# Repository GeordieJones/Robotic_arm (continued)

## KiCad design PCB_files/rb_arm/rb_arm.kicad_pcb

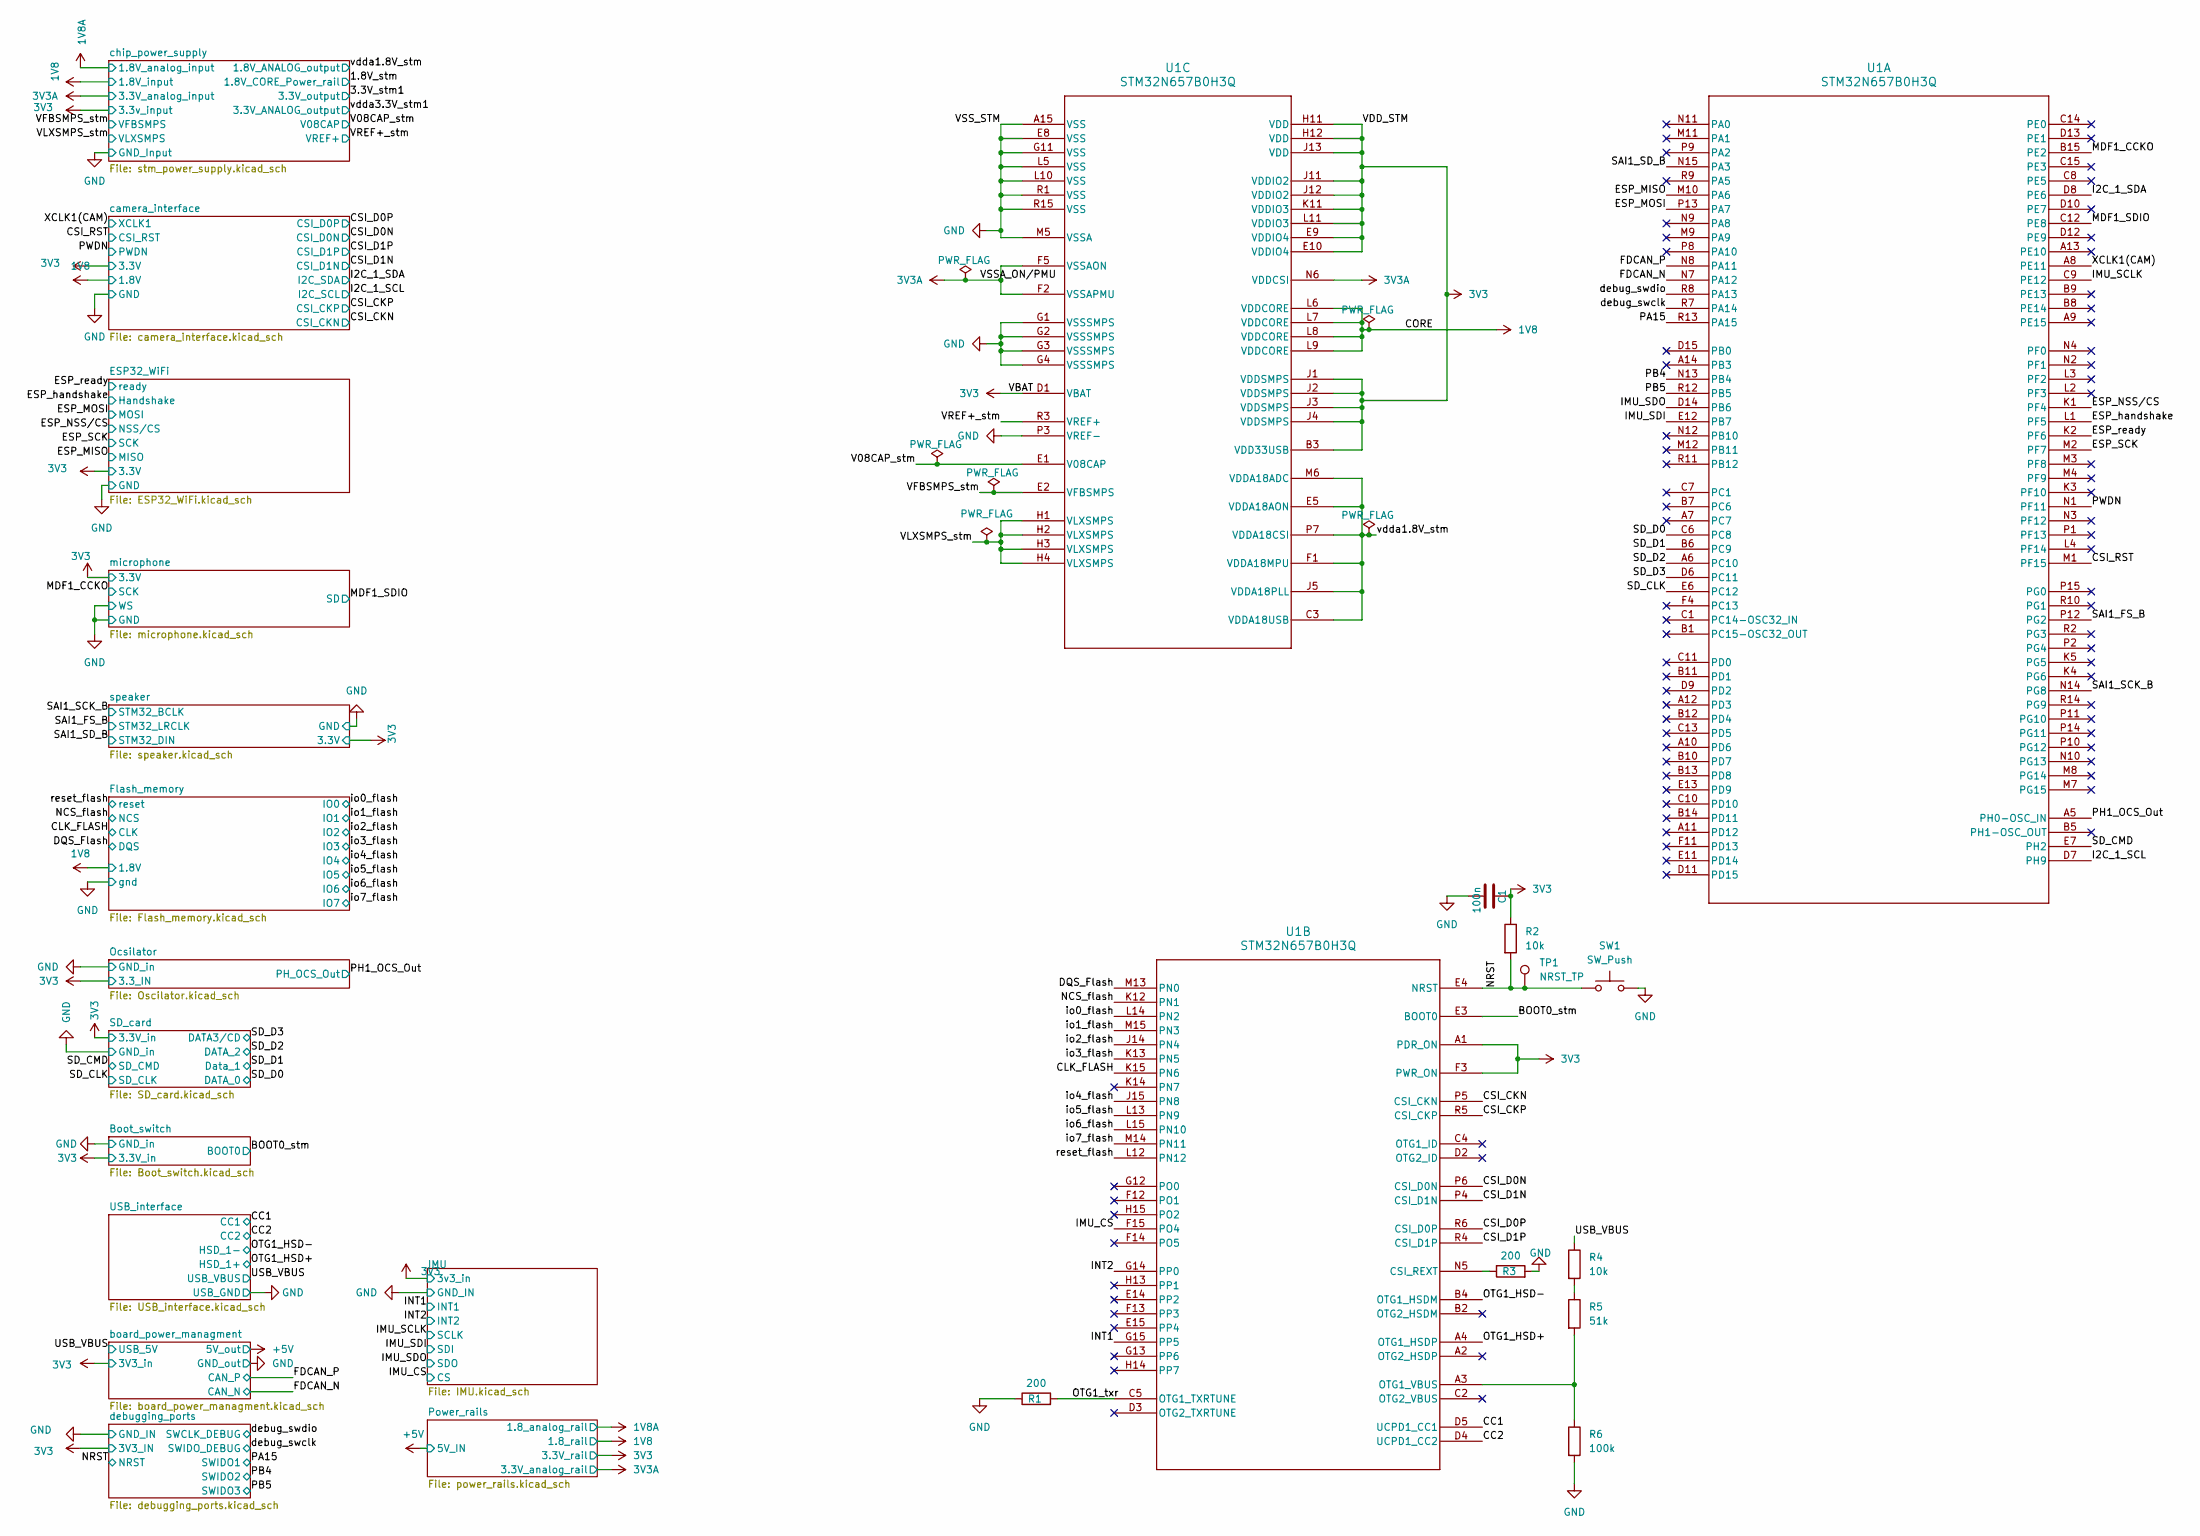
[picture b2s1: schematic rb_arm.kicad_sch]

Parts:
C1: 100n; C_0402_1005Metric; part samsung CL05B104KP5NNNC
R1, R3: 200; R_0402_1005Metric; part number RT0402BRD07200RL
R2, R4: 10k; R_0402_1005Metric; part number Samsung Electro-Mechanics RC1005F103CS
R5: 51k; R_0402_1005Metric; part number YAGEO RC0402FR-0751KL
R6: 100k; R_0402_1005Metric; part number YAGEO RC0402FR-07100KL
SW1: SW_Push; SW_PUSH_6mm_H4.3mm; part number C&K PTS645SM43SMTR92 LFS
TP1: NRST_TP; Pin_D1.0mm_L10.0mm
U1: STM32N657B0H3Q; VFBGA198_10X10_STM

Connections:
1V8: U1.L6 (VDDCORE), U1.L7 (VDDCORE), U1.L8 (VDDCORE), U1.L9 (VDDCORE); also elsewhere on the board
3V3: C1.1, R2.1, U1.A1 (PDR_ON), U1.B3 (VDD33USB), U1.D1 (VBAT), U1.E9 (VDDIO4), U1.E10 (VDDIO4), U1.F3 (PWR_ON), U1.H11 (VDD), U1.H12 (VDD), U1.J1 (VDDSMPS), U1.J2 (VDDSMPS), U1.J3 (VDDSMPS), U1.J4 (VDDSMPS), U1.J11 (VDDIO2), U1.J12 (VDDIO2), U1.J13 (VDD), U1.K11 (VDDIO3), U1.L11 (VDDIO3); also elsewhere on the board
3V3A: U1.F2 (VSSAPMU), U1.F5 (VSSAON), U1.N6 (VDDCSI); also elsewhere on the board
/BOOT0_stm: U1.E3 (BOOT0); also elsewhere on the board
/CC1: U1.D5 (UCPD1_CC1); also elsewhere on the board
/CC2: U1.D4 (UCPD1_CC2); also elsewhere on the board
/CLK_FLASH: U1.K15 (PN6); also elsewhere on the board
/CSI_CKN: U1.P5 (CSI_CKN); also elsewhere on the board
/CSI_CKP: U1.R5 (CSI_CKP); also elsewhere on the board
/CSI_D0N: U1.P6 (CSI_D0N); also elsewhere on the board
/CSI_D0P: U1.R6 (CSI_D0P); also elsewhere on the board
/CSI_D1N: U1.P4 (CSI_D1N); also elsewhere on the board
/CSI_D1P: U1.R4 (CSI_D1P); also elsewhere on the board
/CSI_RST: U1.M1 (PF15); also elsewhere on the board
/DQS_Flash: U1.M13 (PN0); also elsewhere on the board
/ESP_MISO: U1.M10 (PA6); also elsewhere on the board
/ESP_MOSI: U1.P13 (PA7); also elsewhere on the board
/ESP_NSS/CS: U1.K1 (PF4); also elsewhere on the board
/ESP_SCK: U1.M2 (PF7); also elsewhere on the board
/ESP_handshake: U1.L1 (PF5); also elsewhere on the board
/ESP_ready: U1.K2 (PF6); also elsewhere on the board
/FDCAN_N: U1.N7 (PA12); also elsewhere on the board
/FDCAN_P: U1.N8 (PA11); also elsewhere on the board
/I2C_1_SCL: U1.D7 (PH9); also elsewhere on the board
/I2C_1_SDA: U1.D8 (PE6); also elsewhere on the board
/IMU_CS: U1.F15 (PO4); also elsewhere on the board
/IMU_SCLK: U1.C9 (PE12); also elsewhere on the board
/IMU_SDI: U1.E12 (PB7); also elsewhere on the board
/IMU_SDO: U1.D14 (PB6); also elsewhere on the board
/INT1: U1.G15 (PP5); also elsewhere on the board
/INT2: U1.G14 (PP0); also elsewhere on the board
/MDF1_CCKO: U1.B15 (PE2); also elsewhere on the board
/MDF1_SDIO: U1.C12 (PE8); also elsewhere on the board
/NCS_flash: U1.K12 (PN1); also elsewhere on the board
/NRST: R2.2, SW1.1, TP1.1 (1_1), U1.E4 (NRST); also elsewhere on the board
/OTG1_HSD+: U1.A4 (OTG1_HSDP); also elsewhere on the board
/OTG1_HSD-: U1.B4 (OTG1_HSDM); also elsewhere on the board
/OTG1_txr: R1.2, U1.C5 (OTG1_TXRTUNE)
/PA15: U1.R13 (PA15); also elsewhere on the board
/PB4: U1.N13 (PB4); also elsewhere on the board
/PB5: U1.R12 (PB5); also elsewhere on the board
/PH1_OCS_Out: U1.A5 (PH0-OSC_IN); also elsewhere on the board
/PWDN: U1.N1 (PF11); also elsewhere on the board
/SAI1_FS_B: U1.P12 (PG2); also elsewhere on the board
/SAI1_SCK_B: U1.N14 (PG8); also elsewhere on the board
/SAI1_SD_B: U1.N15 (PA3); also elsewhere on the board
/SD_CLK: U1.E6 (PC12); also elsewhere on the board
/SD_CMD: U1.E7 (PH2); also elsewhere on the board
/SD_D0: U1.C6 (PC8); also elsewhere on the board
/SD_D1: U1.B6 (PC9); also elsewhere on the board
/SD_D2: U1.A6 (PC10); also elsewhere on the board
/SD_D3: U1.D6 (PC11); also elsewhere on the board
/USB_VBUS: R4.1; also elsewhere on the board
/V08CAP_stm: U1.E1 (V08CAP); also elsewhere on the board
/VFBSMPS_stm: U1.E2 (VFBSMPS); also elsewhere on the board
/VLXSMPS_stm: U1.H1 (VLXSMPS), U1.H2 (VLXSMPS), U1.H3 (VLXSMPS), U1.H4 (VLXSMPS); also elsewhere on the board
/VREF+_stm: U1.R3 (VREF+); also elsewhere on the board
/XCLK1(CAM): U1.A8 (PE11); also elsewhere on the board
/debug_swclk: U1.R7 (PA14); also elsewhere on the board
/debug_swdio: U1.R8 (PA13); also elsewhere on the board
/io0_flash: U1.L14 (PN2); also elsewhere on the board
/io1_flash: U1.M15 (PN3); also elsewhere on the board
/io2_flash: U1.J14 (PN4); also elsewhere on the board
/io3_flash: U1.K13 (PN5); also elsewhere on the board
/io4_flash: U1.J15 (PN8); also elsewhere on the board
/io5_flash: U1.L13 (PN9); also elsewhere on the board
/io6_flash: U1.L15 (PN10); also elsewhere on the board
/io7_flash: U1.M14 (PN11); also elsewhere on the board
/reset_flash: U1.L12 (PN12); also elsewhere on the board
/vdda1.8V_stm: U1.C3 (VDDA18USB), U1.E5 (VDDA18AON), U1.F1 (VDDA18MPU), U1.J5 (VDDA18PLL), U1.M6 (VDDA18ADC), U1.P7 (VDDA18CSI); also elsewhere on the board
GND: C1.2, R1.1, R3.2, R6.2, SW1.2, U1.A15 (VSS), U1.E8 (VSS), U1.G1 (VSSSMPS), U1.G2 (VSSSMPS), U1.G3 (VSSSMPS), U1.G4 (VSSSMPS), U1.G11 (VSS), U1.L5 (VSS), U1.L10 (VSS), U1.M5 (VSSA), U1.P3 (VREF-), U1.R1 (VSS), U1.R15 (VSS); also elsewhere on the board
unnamed: R4.2, R5.1
unnamed: R3.1, U1.N5 (CSI_REXT)
unnamed: R5.2, R6.1, U1.A3 (OTG1_VBUS)

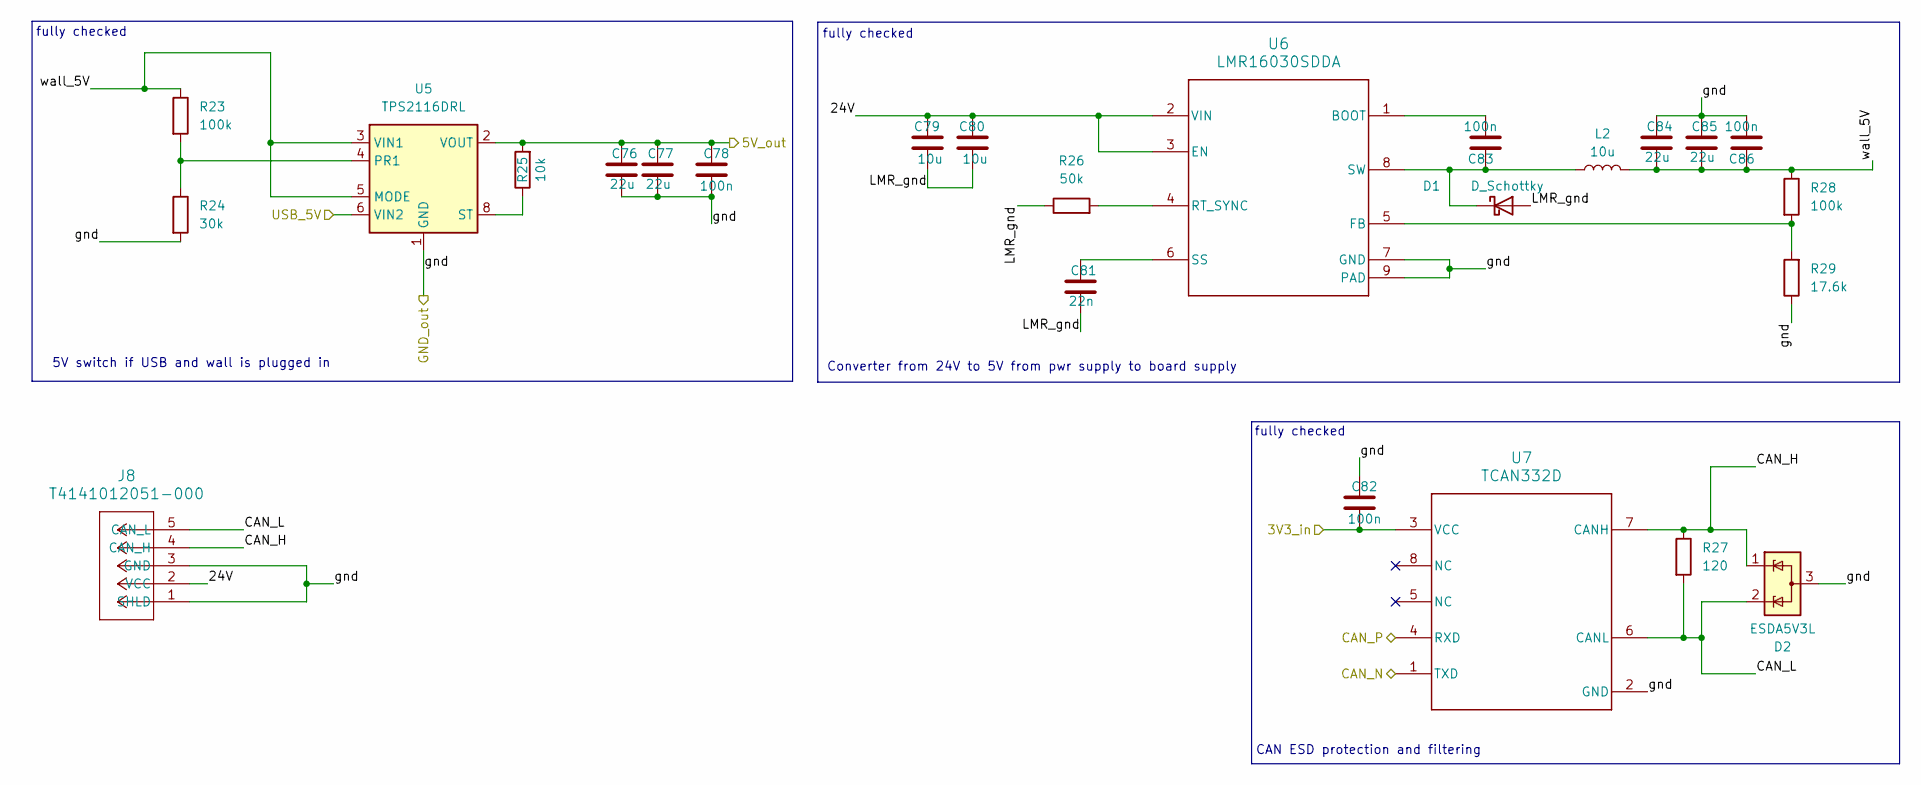
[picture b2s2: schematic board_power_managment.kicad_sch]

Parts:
C76, C77, C84, C85: 22u; C_0402_1005Metric; part Murata Electronics GRM158R61A226ME15D
C78, C82, C83, C86: 100n; C_0402_1005Metric; part samsung CL05B104KP5NNNC
C79, C80: 10u; C_0805_2012Metric; part 0805W106K500CC
C81: 22n; C_0402_1005Metric; part Murata Electronics GRM155R71H223KA12D
D1: D_Schottky; D_SMA
D2: ESDA5V3L; SOT-23-3
J8: T4141012051-000; CONN5_T4141012051
L2: 10u; L_0805_2012Metric
R23, R28: 100k; R_0402_1005Metric; part number YAGEO RC0402FR-07100KL
R24: 30k; R_0402_1005Metric
R25: 10k; R_0402_1005Metric; part number Samsung Electro-Mechanics RC1005F103CS
R26: 50k; R_0603_1608Metric
R27: 120; R_0402_1005Metric
R29: 17.6k; R_0603_1608Metric
U5: TPS2116DRL; SOT-583-8
U6: LMR16030SDDA; DDA0008E_M
U7: TCAN332D; D0008A_N

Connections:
3V3: C82.2, U7.3 (VCC); also elsewhere on the board
+5V: C76.1, C77.1, C78.1, R25.2, U5.2 (VOUT), U5.7 (VOUT); also elsewhere on the board
/FDCAN_N: U7.1 (TXD); also elsewhere on the board
/FDCAN_P: U7.4 (RXD); also elsewhere on the board
/USB_VBUS: U5.6 (VIN2); also elsewhere on the board
/board_power_managment/24V: C79.1, C80.1, J8.2 (VCC), U6.2 (VIN), U6.3 (EN)
/board_power_managment/CAN_H: D2.1 (K), J8.4 (CAN_H), R27.1, U7.7 (CANH)
/board_power_managment/CAN_L: D2.2 (K), J8.5 (CAN_L), R27.2, U7.6 (CANL)
/board_power_managment/LMR_gnd: C79.2, C80.2, C81.2, D1.2 (A), R26.1
/board_power_managment/wall_5V: C84.2, C85.2, C86.1, L2.2, R23.1, R28.1, U5.3 (VIN1), U5.5 (MODE)
GND: C76.2, C77.2, C78.2, C82.1, C84.1, C85.1, C86.2, D2.3 (A), J8.1 (SHLD), J8.3 (GND), R24.2, R29.1, U5.1 (GND), U6.7 (GND), U6.9 (PAD), U6.V, U7.2 (GND); also elsewhere on the board
unnamed: C83.1, D1.1 (K), L2.1, U6.8 (SW)
unnamed: R23.2, R24.1, U5.4 (PR1)
unnamed: R25.1, U5.8 (ST)
unnamed: C83.2, U6.1 (BOOT)
unnamed: R28.2, R29.2, U6.5 (FB)
unnamed: R26.2, U6.4 (RT_SYNC)
unnamed: C81.1, U6.6 (SS)

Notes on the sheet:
fully checked
CAN ESD protection and filtering
Converter from 24V to 5V from pwr supply to board supply
5V switch if USB and wall is plugged in

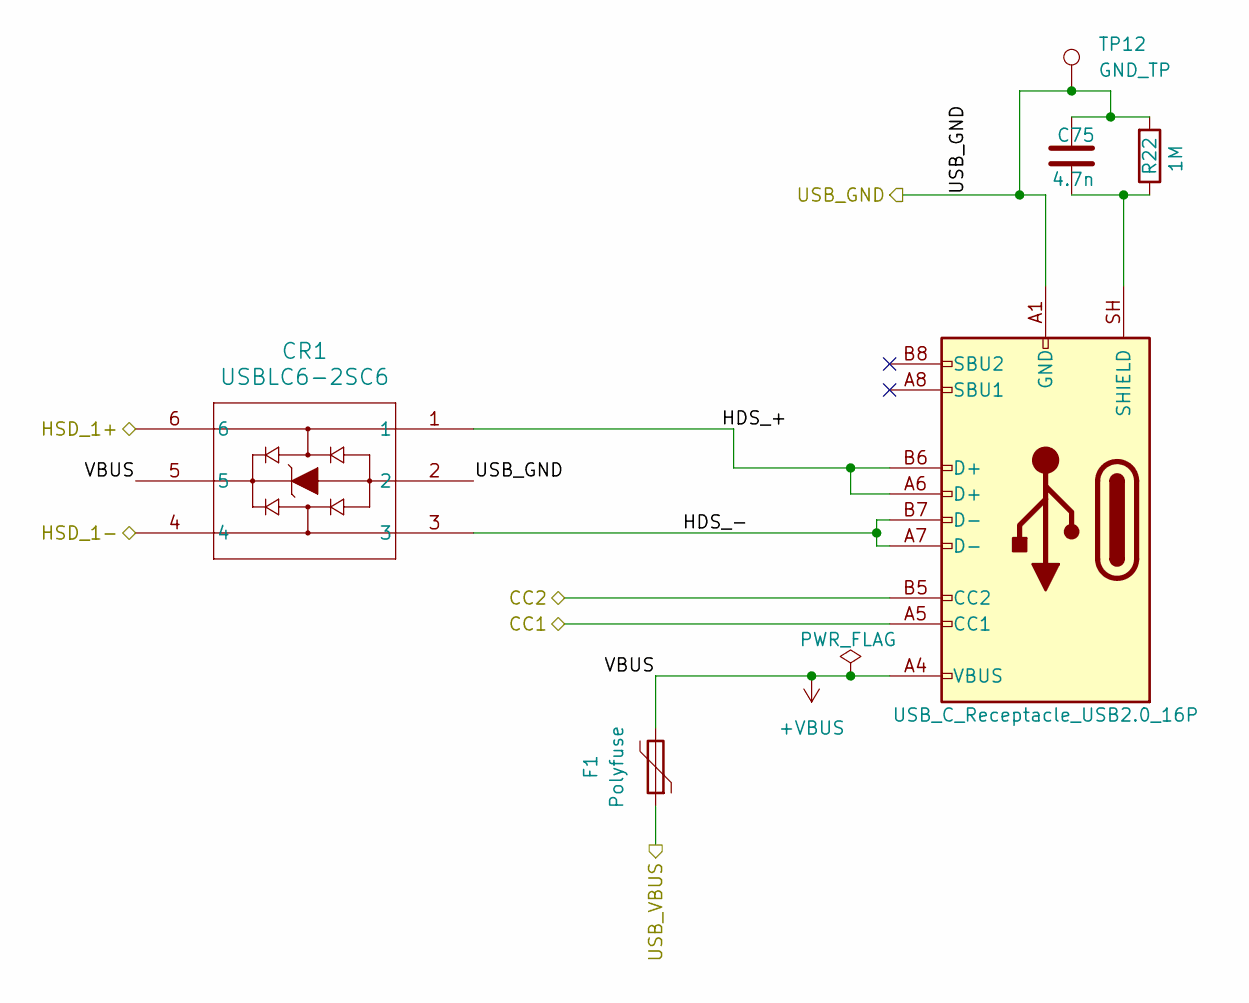
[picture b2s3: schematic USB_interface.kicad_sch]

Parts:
C75: 4.7n; LED_0603_1608Metric
CR1: USBLC6-2SC6; SOT23-6L_STM-M
F1: Polyfuse; Fuse_1206_3216Metric; part Bourns Inc. MF-NSMF110-2
J7: USB_C_Receptacle_USB2.0_16P; USB_C_Receptacle_GCT_USB4105-xx-A_16P_TopMnt_Horizontal; part USB4105-GF-A
R22: 1M; R_0402_1005Metric; part number YAGEO RC0402FR-071ML
TP12: GND_TP; Pin_D1.0mm_L10.0mm

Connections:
+VBUS: CR1.5, F1.2, J7.A4 (VBUS), J7.A9 (VBUS), J7.B4 (VBUS), J7.B9 (VBUS)
/CC1: J7.A5 (CC1); also elsewhere on the board
/CC2: J7.B5 (CC2); also elsewhere on the board
/OTG1_HSD+: CR1.6; also elsewhere on the board
/OTG1_HSD-: CR1.4; also elsewhere on the board
/USB_VBUS: F1.1; also elsewhere on the board
/USB_interface/HDS_+: CR1.1, J7.A6 (D+), J7.B6 (D+)
/USB_interface/HDS_-: CR1.3, J7.A7 (D-), J7.B7 (D-)
GND: C75.1, CR1.2, J7.A1 (GND), J7.A12 (GND), J7.B1 (GND), J7.B12 (GND), R22.2, TP12.1 (1_1); also elsewhere on the board
unnamed: C75.2, J7.SH (SHIELD), R22.1

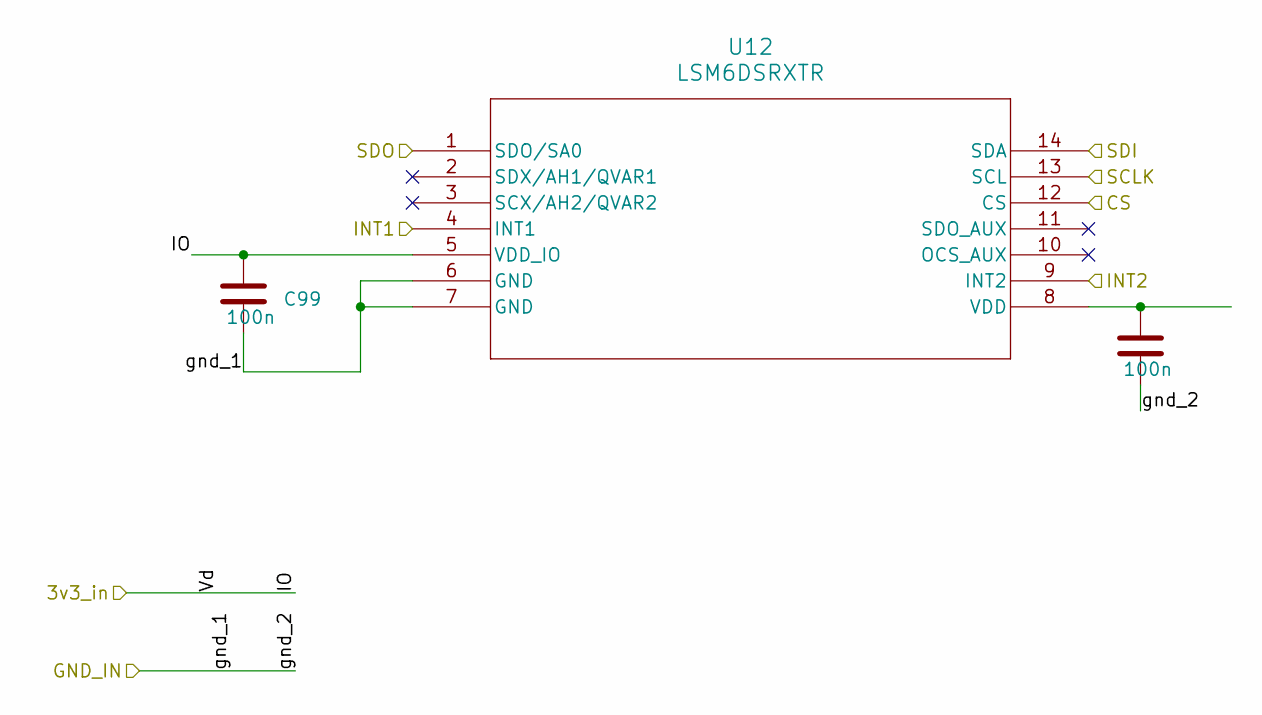
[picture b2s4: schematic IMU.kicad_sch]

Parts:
C98, C99: 100n; C_0402_1005Metric; part samsung CL05B104KP5NNNC
U12: LSM6DSRXTR; LGA-14L_STM-M

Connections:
3V3: C99.1, U12.5 (VDD_IO); also elsewhere on the board
/IMU_CS: U12.12 (CS); also elsewhere on the board
/IMU_SCLK: U12.13 (SCL); also elsewhere on the board
/IMU_SDI: U12.14 (SDA); also elsewhere on the board
/IMU_SDO: U12.1 (SDO/SA0); also elsewhere on the board
/INT1: U12.4 (INT1); also elsewhere on the board
/INT2: U12.9 (INT2); also elsewhere on the board
GND: C98.2, C99.2, U12.6 (GND), U12.7 (GND); also elsewhere on the board
unnamed: C98.1, U12.8 (VDD)

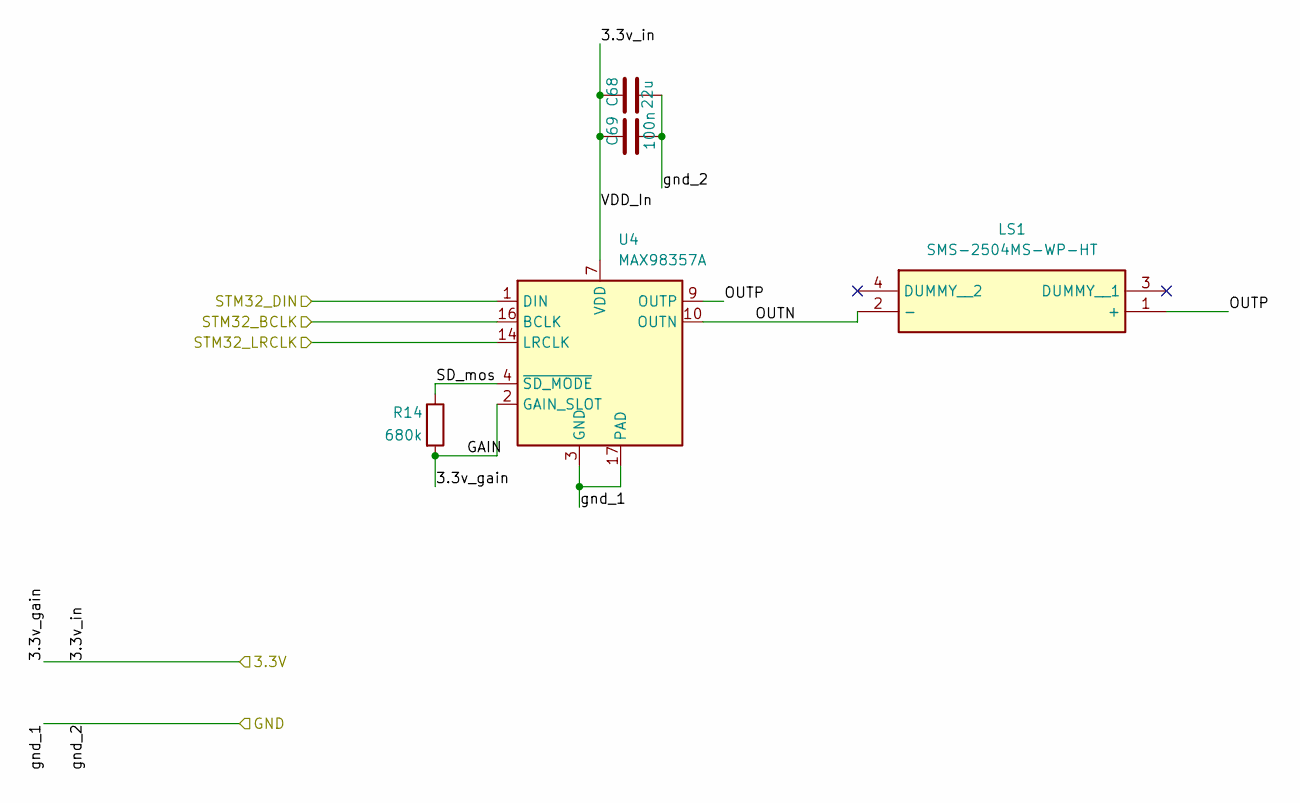
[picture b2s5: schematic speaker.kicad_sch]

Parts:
C68: 22u; C_0402_1005Metric; part Murata Electronics GRM158R61A226ME15D
C69: 100n; C_0402_1005Metric; part samsung CL05B104KP5NNNC
LS1: SMS-2504MS-WP-HT; SMS2504MSWPHT; Manufacturer_Part_Number SMS-2504MS-WP-HT; Mouser Part Number 665-SMS-2504MS-WP-HT
R14: 680k; R_0402_1005Metric; part number YAGEO RC0402FR-07680KL
U4: MAX98357A; TQFN-16-1EP_3x3mm_P0.5mm_EP1.23x1.23mm

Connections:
3V3: C68.1, C69.1, R14.2, U4.2 (GAIN_SLOT), U4.7 (VDD), U4.8 (VDD); also elsewhere on the board
/SAI1_FS_B: U4.14 (LRCLK); also elsewhere on the board
/SAI1_SCK_B: U4.16 (BCLK); also elsewhere on the board
/SAI1_SD_B: U4.1 (DIN); also elsewhere on the board
/speaker/OUTN: LS1.2 (-), U4.10 (OUTN)
/speaker/OUTP: LS1.1 (+), U4.9 (OUTP)
/speaker/SD_mos: R14.1, U4.4 (~SD_MODE)
GND: C68.2, C69.2, U4.3 (GND), U4.11 (GND), U4.15 (GND), U4.17 (PAD); also elsewhere on the board

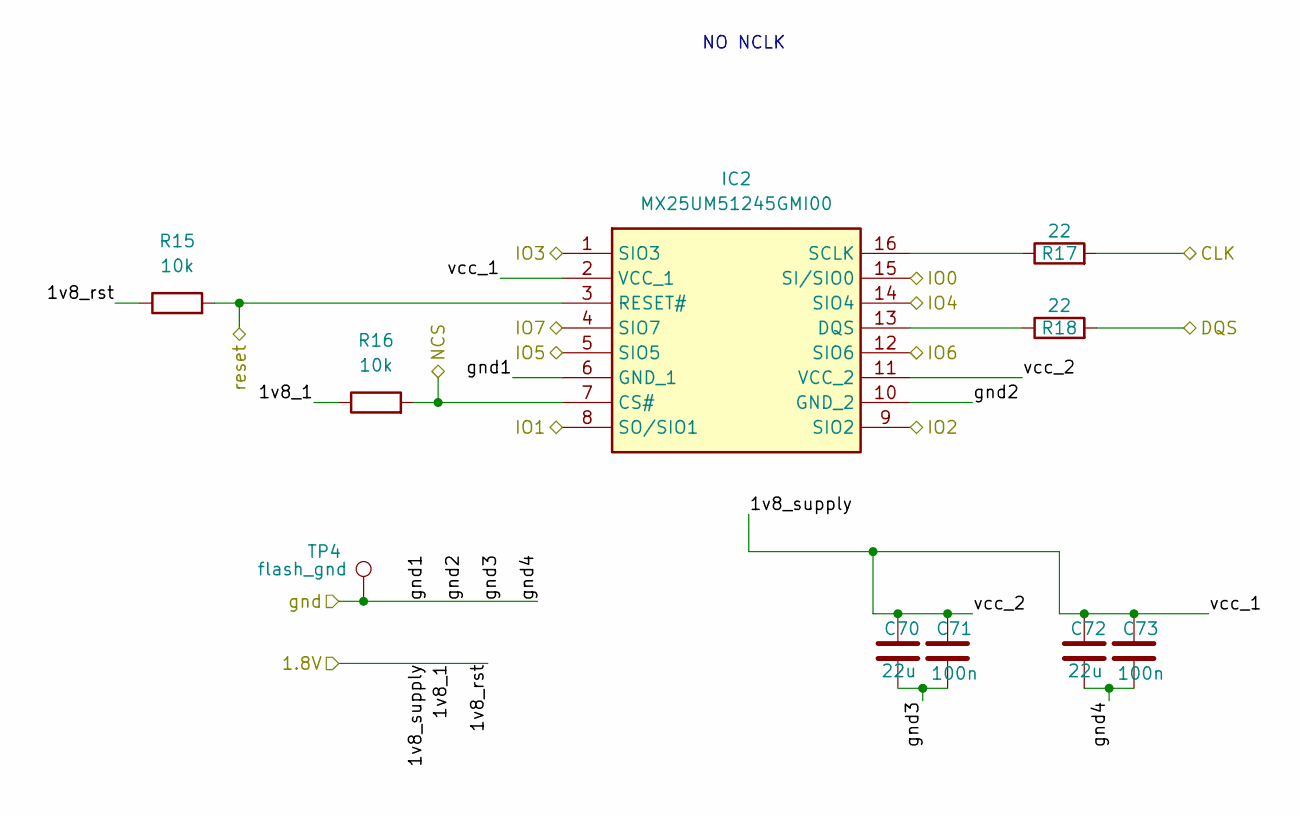
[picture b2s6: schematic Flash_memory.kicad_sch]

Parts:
C70, C72: 22u; C_0402_1005Metric; part Murata Electronics GRM158R61A226ME15D
C71, C73: 100n; C_0402_1005Metric; part samsung CL05B104KP5NNNC
IC2: MX25UM51245GMI00; SOIC127P1030X265-16N; Manufacturer_Part_Number MX25UM51245GMI00
R15, R16: 10k; R_0402_1005Metric; part number Samsung Electro-Mechanics RC1005F103CS
R17, R18: 22; R_0402_1005Metric; part number YAGEO RC0402FR-0722RL
TP4: flash_gnd; Pin_D1.0mm_L10.0mm

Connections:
1V8: C70.1, C71.1, C72.1, C73.1, IC2.2 (VCC_1), IC2.11 (VCC_2), R15.1, R16.1; also elsewhere on the board
/CLK_FLASH: R17.2; also elsewhere on the board
/DQS_Flash: R18.2; also elsewhere on the board
/NCS_flash: IC2.7 (CS#), R16.2; also elsewhere on the board
/io0_flash: IC2.15 (SI/SIO0); also elsewhere on the board
/io1_flash: IC2.8 (SO/SIO1); also elsewhere on the board
/io2_flash: IC2.9 (SIO2); also elsewhere on the board
/io3_flash: IC2.1 (SIO3); also elsewhere on the board
/io4_flash: IC2.14 (SIO4); also elsewhere on the board
/io5_flash: IC2.5 (SIO5); also elsewhere on the board
/io6_flash: IC2.12 (SIO6); also elsewhere on the board
/io7_flash: IC2.4 (SIO7); also elsewhere on the board
/reset_flash: IC2.3 (RESET#), R15.2; also elsewhere on the board
GND: C70.2, C71.2, C72.2, C73.2, IC2.6 (GND_1), IC2.10 (GND_2), TP4.1 (1_1); also elsewhere on the board
unnamed: IC2.13 (DQS), R18.1
unnamed: IC2.16 (SCLK), R17.1

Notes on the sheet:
NO NCLK

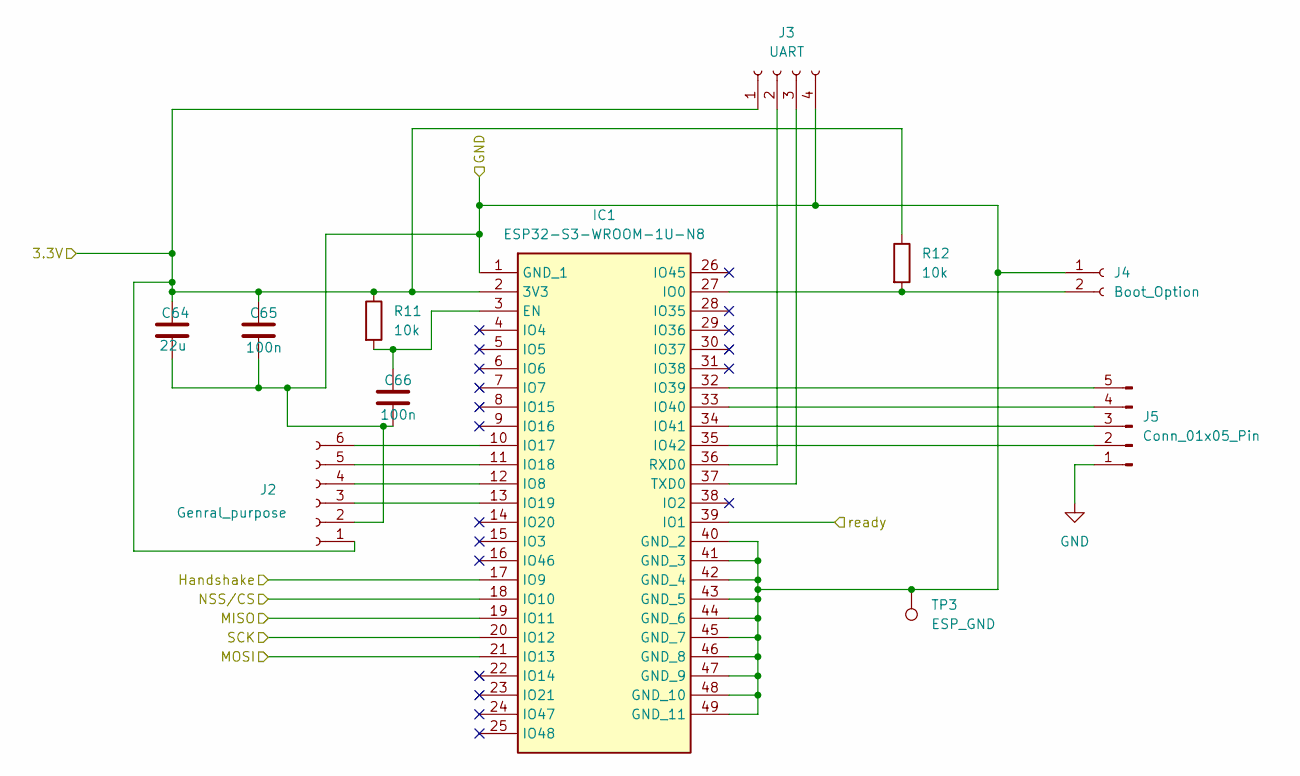
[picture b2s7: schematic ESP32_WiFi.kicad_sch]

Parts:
C64: 22u; C_0402_1005Metric; part Murata Electronics GRM158R61A226ME15D
C65, C66: 100n; C_0402_1005Metric; part samsung CL05B104KP5NNNC
IC1: ESP32-S3-WROOM-1U-N8; ESP32S3WROOM1UN8; Manufacturer_Part_Number ESP32-S3-WROOM-1U-N8; Mouser Part Number 356-ESP32S3WROOM1UN8
J2: Genral_purpose; PinSocket_1x06_P2.54mm_Vertical
J3: UART; PinSocket_1x04_P2.54mm_Vertical
J4: Boot_Option; PinSocket_1x02_P2.00mm_Vertical
J5: Conn_01x05_Pin; PinSocket_1x05_P2.54mm_Vertical
R11, R12: 10k; R_0402_1005Metric; part number Samsung Electro-Mechanics RC1005F103CS
TP3: ESP_GND; Pin_D1.0mm_L10.0mm

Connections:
3V3: C64.1, C65.1, IC1.2 (3V3), J2.1, J3.1, R11.1, R12.1; also elsewhere on the board
/ESP_MISO: IC1.19 (IO11); also elsewhere on the board
/ESP_MOSI: IC1.21 (IO13); also elsewhere on the board
/ESP_NSS/CS: IC1.18 (IO10); also elsewhere on the board
/ESP_SCK: IC1.20 (IO12); also elsewhere on the board
/ESP_handshake: IC1.17 (IO9); also elsewhere on the board
/ESP_ready: IC1.39 (IO1); also elsewhere on the board
GND: C64.2, C65.2, C66.2, IC1.1 (GND_1), IC1.40 (GND_2), IC1.41 (GND_3), IC1.42 (GND_4), IC1.43 (GND_5), IC1.44 (GND_6), IC1.45 (GND_7), IC1.46 (GND_8), IC1.47 (GND_9), IC1.48 (GND_10), IC1.49 (GND_11), J2.2, J3.4, J4.1, J5.1, TP3.1 (1_1); also elsewhere on the board
unnamed: C66.1, IC1.3 (EN), R11.2
unnamed: IC1.27 (IO0), J4.2, R12.2
unnamed: IC1.12 (IO8), J2.4
unnamed: IC1.10 (IO17), J2.6
unnamed: IC1.11 (IO18), J2.5
unnamed: IC1.13 (IO19), J2.3
unnamed: IC1.32 (IO39), J5.5
unnamed: IC1.33 (IO40), J5.4
unnamed: IC1.34 (IO41), J5.3
unnamed: IC1.35 (IO42), J5.2
unnamed: IC1.36 (RXD0), J3.2
unnamed: IC1.37 (TXD0), J3.3

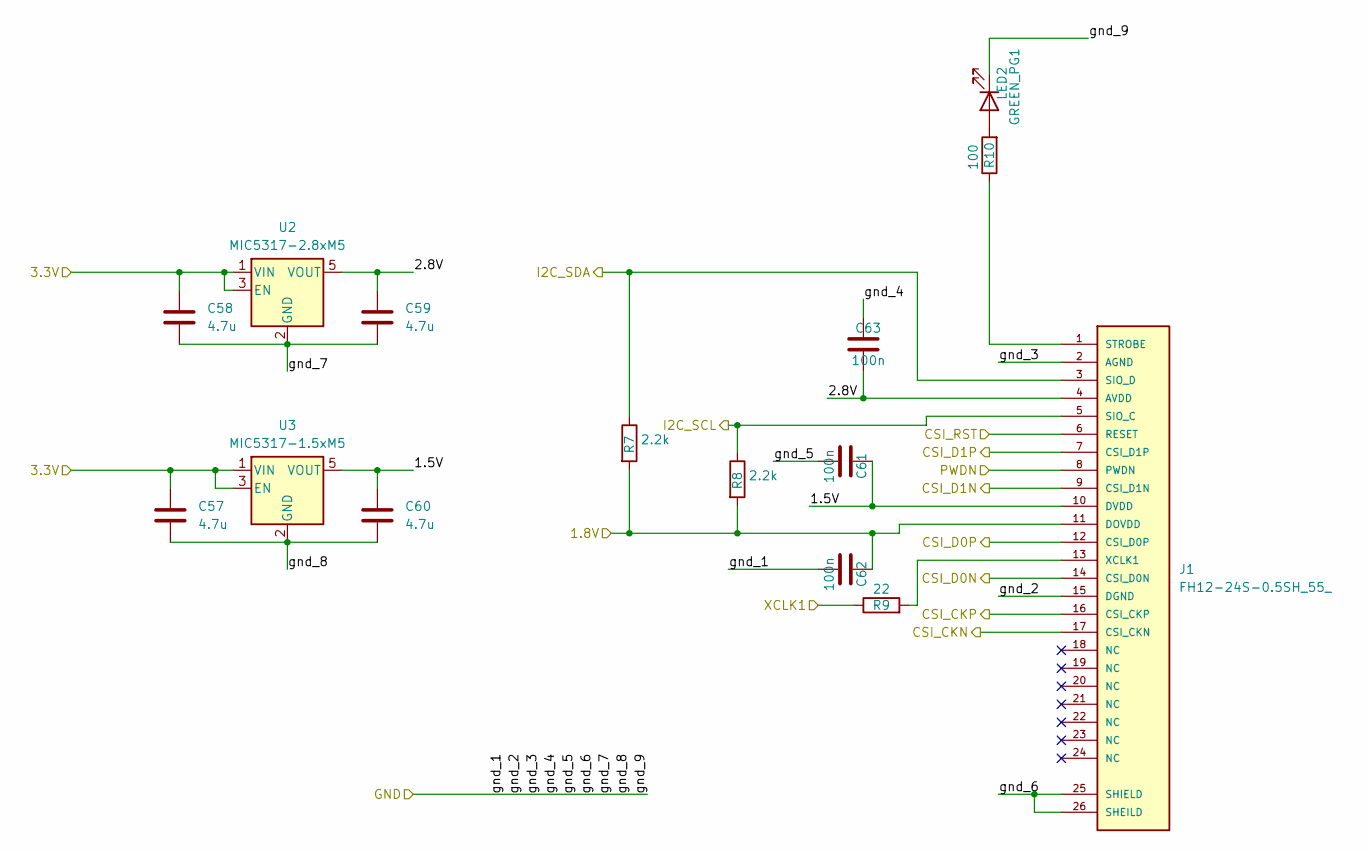
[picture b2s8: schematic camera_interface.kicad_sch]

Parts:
C57, C58, C59, C60: 4.7u; C_0402_1005Metric; part Samsung Electro-Mechanics CL05A475MP5NR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
C61, C62, C63: 100n; C_0402_1005Metric; part samsung CL05B104KP5NNNC
GREEN_PG1: LED2; LED_0603_1608Metric; Part number Kingbright APT1608EC
J1: FH12-24S-0.5SH_55_; FH12-24S-0.5SH_55
R7, R8: 2.2k; R_0402_1005Metric; part number YAGEO RC0402FR-072K2L
R9: 22; R_0402_1005Metric; part number YAGEO RC0402FR-0722RL
R10: 100; R_0402_1005Metric; part number YAGEO RC0402FR-07100RL
U2: MIC5317-2.8xM5; SOT-23-5
U3: MIC5317-1.5xM5; SOT-23-5

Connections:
1V8: C62.1, J1.11 (DOVDD), R7.2, R8.2; also elsewhere on the board
3V3: C57.1, C58.1, U2.1 (VIN), U2.3 (EN), U3.1 (VIN), U3.3 (EN); also elsewhere on the board
/CSI_CKN: J1.17 (CSI_CKN); also elsewhere on the board
/CSI_CKP: J1.16 (CSI_CKP); also elsewhere on the board
/CSI_D0N: J1.14 (CSI_D0N); also elsewhere on the board
/CSI_D0P: J1.12 (CSI_D0P); also elsewhere on the board
/CSI_D1N: J1.9 (CSI_D1N); also elsewhere on the board
/CSI_D1P: J1.7 (CSI_D1P); also elsewhere on the board
/CSI_RST: J1.6 (RESET); also elsewhere on the board
/I2C_1_SCL: J1.5 (SIO_C), R8.1; also elsewhere on the board
/I2C_1_SDA: J1.3 (SIO_D), R7.1; also elsewhere on the board
/PWDN: J1.8 (PWDN); also elsewhere on the board
/XCLK1(CAM): R9.1; also elsewhere on the board
/camera_interface/1.5V: C60.1, C61.1, J1.10 (DVDD), U3.5 (VOUT)
/camera_interface/2.8V: C59.1, C63.2, J1.4 (AVDD), U2.5 (VOUT)
GND: C57.2, C58.2, C59.2, C60.2, C61.2, C62.2, C63.1, GREEN_PG1.1 (K), J1.2 (AGND), J1.15 (DGND), J1.25 (SHIELD), J1.26 (SHEILD), U2.2 (GND), U3.2 (GND); also elsewhere on the board
unnamed: GREEN_PG1.2 (A), R10.2
unnamed: J1.1 (STROBE), R10.1
unnamed: J1.13 (XCLK1), R9.2

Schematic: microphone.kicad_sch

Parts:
C67: 100n; C_0402_1005Metric; part samsung CL05B104KP5NNNC
MK1: ICS-43434; InvenSense_ICS-43434-6_3.5x2.65mm
R13: 100k; R_0402_1005Metric; part number YAGEO RC0402FR-07100KL

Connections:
3V3: C67.1, MK1.5 (VDD); also elsewhere on the board
/MDF1_CCKO: MK1.4 (SCK); also elsewhere on the board
/MDF1_SDIO: MK1.6 (SD), R13.1; also elsewhere on the board
GND: C67.2, MK1.1 (WS), MK1.2 (LR), MK1.3 (GND), R13.2; also elsewhere on the board

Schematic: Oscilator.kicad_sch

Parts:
Y1: ECS-3963-160-AU-TR; OSC_ECS-3963-160-AU-TR; PARTREV N/A

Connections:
3V3: Y1.4 (VDD); also elsewhere on the board
/PH1_OCS_Out: Y1.3 (OUTPUT); also elsewhere on the board
GND: Y1.2 (GND); also elsewhere on the board

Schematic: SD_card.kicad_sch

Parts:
C74: 4.7u; C_0402_1005Metric; part Samsung Electro-Mechanics CL05A475MP5NR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
J6: Micro_SD_Card_Det1; microSD_HC_Molex_104031-0811
R19: 10k; R_0402_1005Metric; part number Samsung Electro-Mechanics RC1005F103CS
R20: 1M; R_0402_1005Metric; part number YAGEO RC0402FR-071ML
TP5: TestPoint; Pin_D1.0mm_L10.0mm

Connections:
3V3: J6.4 (VDD), R19.1; also elsewhere on the board
/SD_CLK: J6.5 (CLK); also elsewhere on the board
/SD_CMD: J6.3 (CMD); also elsewhere on the board
/SD_D0: J6.7 (DAT0); also elsewhere on the board
/SD_D1: J6.8 (DAT1); also elsewhere on the board
/SD_D2: J6.1 (DAT2); also elsewhere on the board
/SD_D3: J6.2 (DAT3/CD); also elsewhere on the board
GND: C74.1, J6.6 (VSS), R20.2; also elsewhere on the board
unnamed: J6.9 (DET), R19.2, TP5.1 (1_1)
unnamed: C74.2, J6.SH (SHEILD_2), R20.1

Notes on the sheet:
SDMMC1_D1
SDMMC1_CMD
SD CARD
SDMMC1_GPIO_card_detect
SDMMC1_CK
SDMMC1_D3
SDMMC1_D0
SDMMC1_D2

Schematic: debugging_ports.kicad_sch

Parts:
C87: 100n; C_0402_1005Metric; part samsung CL05B104KP5NNNC
J9, J10: Conn_01x05_Pin; PinHeader_1x05_P2.54mm_Vertical

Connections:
3V3: J9.5, J10.5; also elsewhere on the board
/NRST: C87.1; also elsewhere on the board
/PA15: J9.2; also elsewhere on the board
/PB4: J9.3; also elsewhere on the board
/PB5: J9.4; also elsewhere on the board
/debug_swclk: J10.3; also elsewhere on the board
/debug_swdio: J10.4; also elsewhere on the board
GND: J9.1, J10.1; also elsewhere on the board
unnamed: C87.2, J10.2

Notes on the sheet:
SWDIO_DEBUGING
PWR
DEBUG

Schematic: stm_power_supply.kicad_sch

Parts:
C2, C3, C4, C5, C6, C7, C12, C13, C14, C15, C16, C17, C18, C22, C23, C24, C25, C26, C27, C28, C29, C30, C31, C32, C33, C34, C35, C36, C37, C38, C39, C40, C41, C42, C43, C44, C45, C46, C49, C50, C51, C52, C53, C54: 100n; C_0402_1005Metric; part samsung CL05B104KP5NNNC
C8, C9, C10, C11, C19, C20, C21, C47, C48, C55, C56: 22u; C_0402_1005Metric; part Murata Electronics GRM158R61A226ME15D
FB1, FB2: 120ohm; L_0603_1608Metric; part Murata Electronics BLM18AG121SN1D
L1: 2.2u; L_Wuerth_MAPI-4020
TP2: VCAP; Pin_D1.0mm_L10.0mm

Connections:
1V8: C2.1, C3.1, C4.1, C5.1, C6.1, C7.1, C8.2, C9.2, C10.2, C11.2; also elsewhere on the board
1V8A: C56.2, FB2.1; also elsewhere on the board
3V3: C22.1, C23.1, C24.1, C25.1, C26.1, C27.1, C28.1, C29.1, C30.1, C31.1, C32.1, C33.1, C34.1, C35.1, C36.1, C37.1, C38.1, C39.1, C40.1, C41.1, C42.1, C43.1, C44.1, C45.1, C46.1, C47.2; also elsewhere on the board
3V3A: C12.1, C13.1, C14.1, C15.1, C16.1, C17.1, C18.1, C19.2, C20.2, C21.2, FB1.1, FB1.2; also elsewhere on the board
/V08CAP_stm: C48.1, TP2.1 (1_1); also elsewhere on the board
/VFBSMPS_stm: L1.1; also elsewhere on the board
/VLXSMPS_stm: L1.2; also elsewhere on the board
/VREF+_stm: C12.2, C21.1; also elsewhere on the board
/vdda1.8V_stm: C49.1, C50.1, C51.1, C52.1, C53.1, C54.1, C55.2, FB2.2; also elsewhere on the board
GND: C2.2, C3.2, C4.2, C5.2, C6.2, C7.2, C8.1, C9.1, C10.1, C11.1, C13.2, C14.2, C15.2, C16.2, C17.2, C18.2, C19.1, C20.1, C22.2, C23.2, C24.2, C25.2, C26.2, C27.2, C28.2, C29.2, C30.2, C31.2, C32.2, C33.2, C34.2, C35.2, C36.2, C37.2, C38.2, C39.2, C40.2, C41.2, C42.2, C43.2, C44.2, C45.2, C46.2, C47.1, C48.2, C49.2, C50.2, C51.2, C52.2, C53.2, C54.2, C55.1, C56.1; also elsewhere on the board

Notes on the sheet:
GND
STMN6 POWER SUPPLY
VDD Analog 3.3V power rail
25 100nF 1 22uF
6 100nF 1 22uF
V08CAP rail
VREF rail
VDD Direct 3.3V rail
VDD Analog 3.3V power rail
10 pins to 1.8
6 100nF 4 22uF
1.8V powercore rail
